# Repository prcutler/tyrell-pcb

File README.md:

# tyrell-pcb
PCB Design files for a carrier PCB for the [Adafruit Tyrell Desktop Synthesizer](https://learn.adafruit.com/tyrell-desktop-synthesizer) project.

Hardware needed:

* [Adafruit rp2040 Feather](https://www.adafruit.com/product/4884) - $12
* [PCM5102A I2S DAC](https://amzn.to/3My0USS) - 3 for $15 (affiliate link)
* [Copper foil tape with conductive adhesive](https://www.adafruit.com/product/3483) - $5

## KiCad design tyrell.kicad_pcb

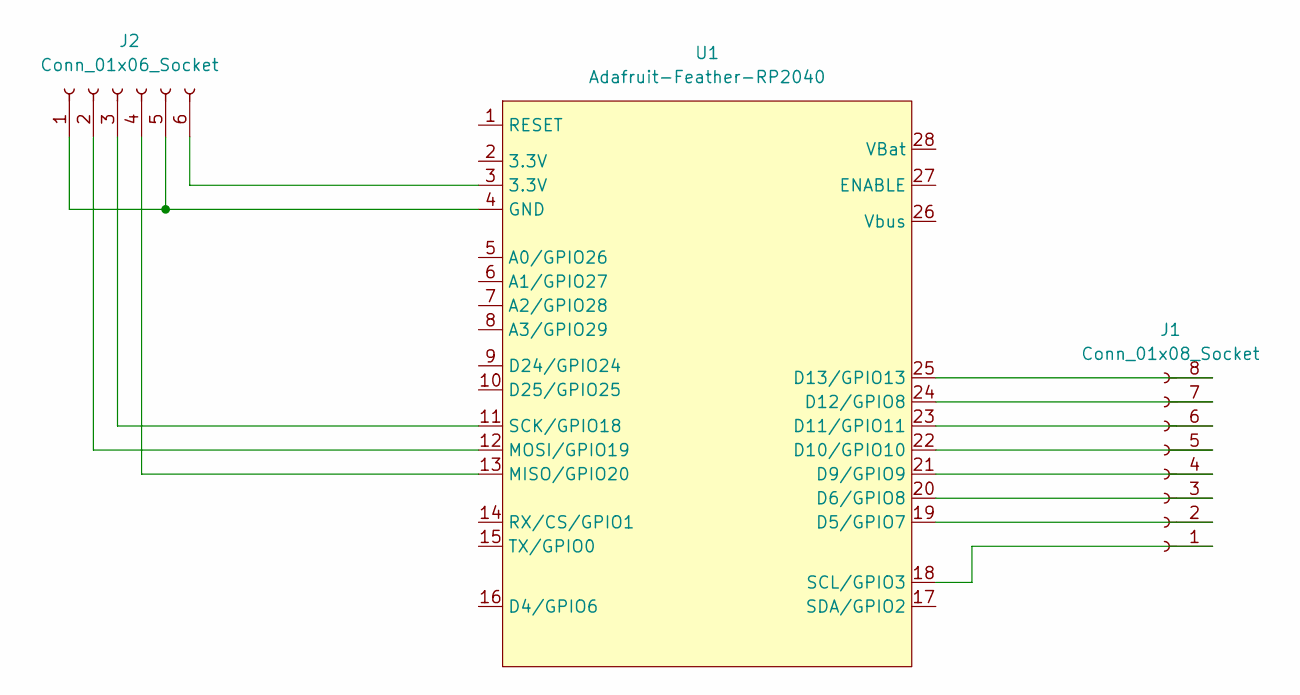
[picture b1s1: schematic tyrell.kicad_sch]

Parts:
J1: Conn_01x08_Socket; PinSocket_1x08_P2.54mm_Horizontal
J2: Conn_01x06_Socket; PinHeader_1x06_P2.54mm_Horizontal
U1: Adafruit-Feather-RP2040; Adafruit_Feather

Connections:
unnamed: J1.1, U1.18 (SCL/GPIO3)
unnamed: J1.2, U1.19 (D5/GPIO7)
unnamed: J1.3, U1.20 (D6/GPIO8)
unnamed: J1.4, U1.21 (D9/GPIO9)
unnamed: J1.5, U1.22 (D10/GPIO10)
unnamed: J1.6, U1.23 (D11/GPIO11)
unnamed: J1.7, U1.24 (D12/GPIO8)
unnamed: J1.8, U1.25 (D13/GPIO13)
unnamed: J2.1, J2.5, U1.4 (GND)
unnamed: J2.2, U1.12 (MOSI/GPIO19)
unnamed: J2.3, U1.11 (SCK/GPIO18)
unnamed: J2.4, U1.13 (MISO/GPIO20)
unnamed: J2.6, U1.3 (3.3V)

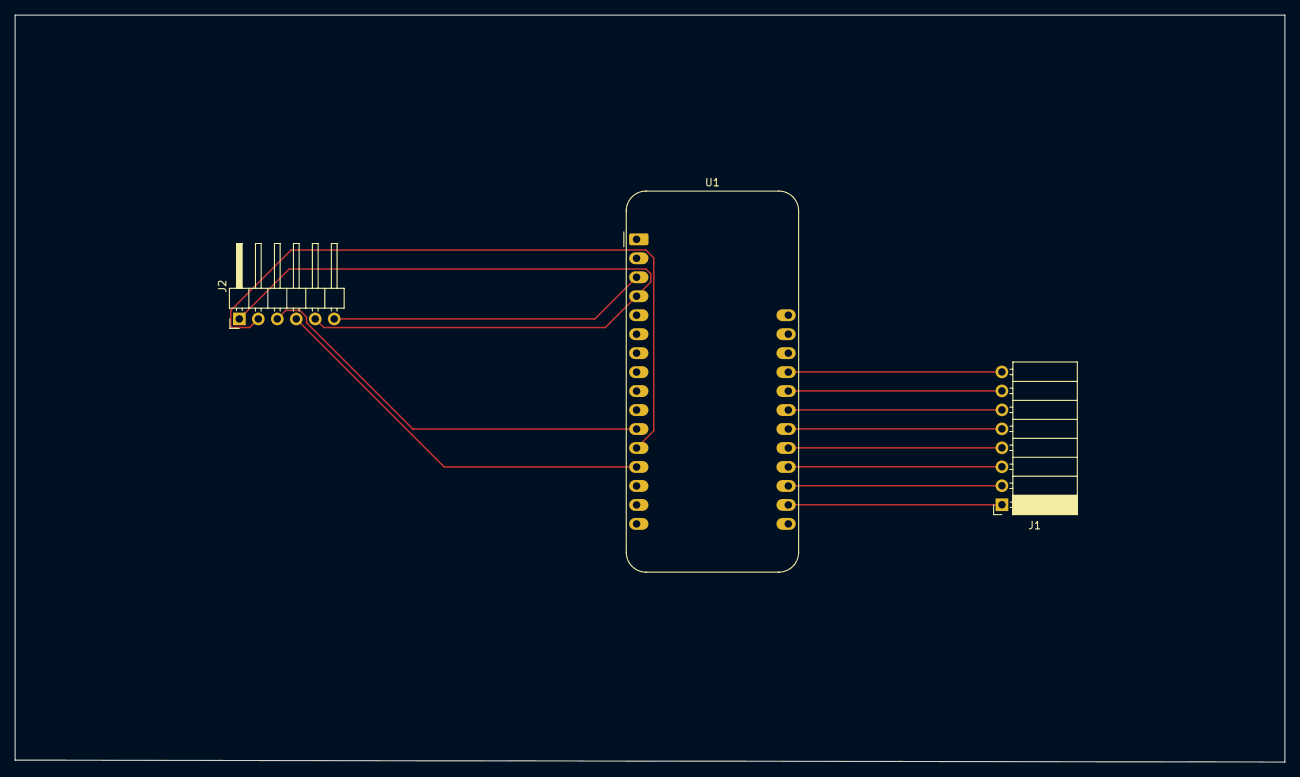
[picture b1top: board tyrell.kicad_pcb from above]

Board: 2 copper layers, 170.0 x 100.0 mm, 3 parts (0 on the bottom side), 13 nets.

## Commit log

2024-09-19 Add working 80s dystopia code from todbot
